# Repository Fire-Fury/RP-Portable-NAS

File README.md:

# RP-Portable-NAS
An attempt at making a personal cloud device with the form factor of a Raspberry Pi 4.

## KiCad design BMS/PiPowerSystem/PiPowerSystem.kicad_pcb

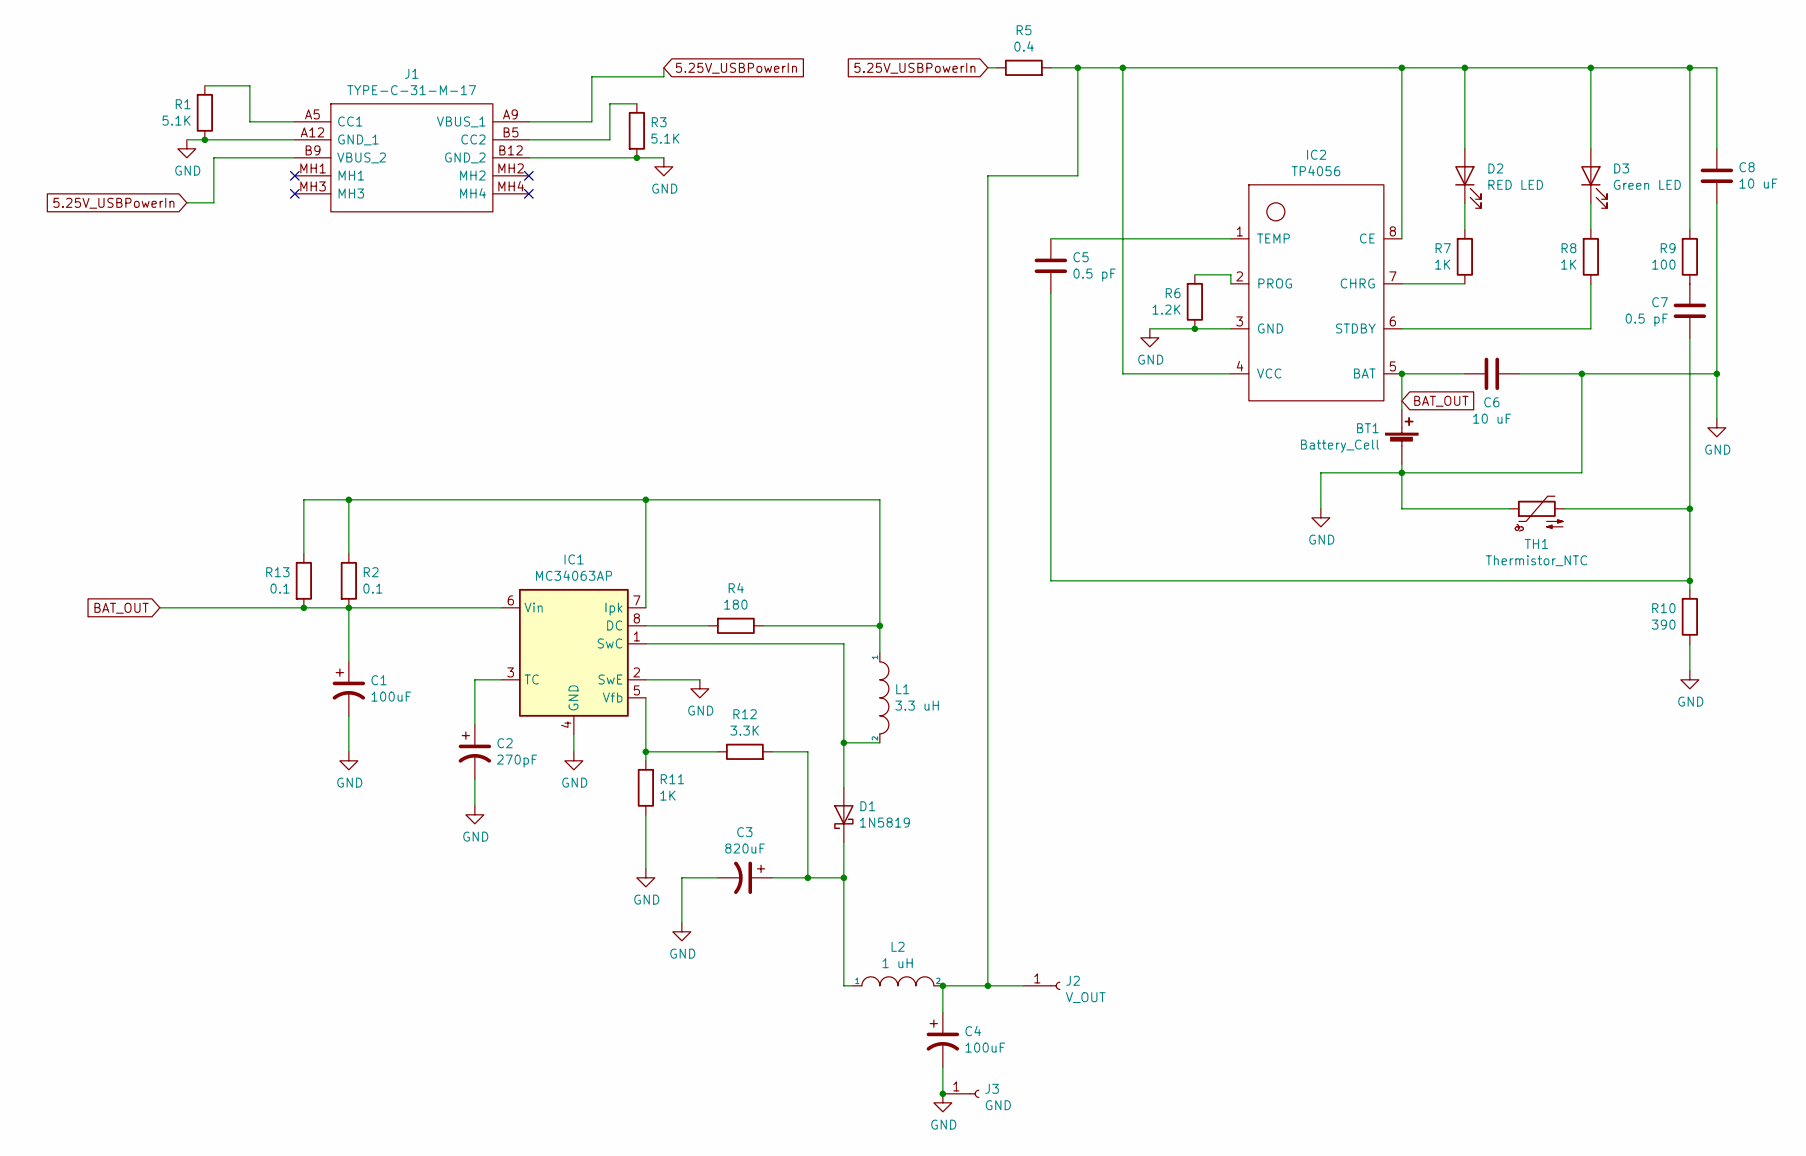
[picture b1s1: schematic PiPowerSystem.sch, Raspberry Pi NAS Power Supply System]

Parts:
BT1: Battery_Cell; JST_PH_B2B-PH-K_1x02_P2.00mm_Vertical
C1, C4: 100uF; CP_Radial_D8.0mm_P3.50mm
C2: 270pF; C_Disc_D5.1mm_W3.2mm_P5.00mm
C3: 820uF; CP_Radial_D10.0mm_P5.00mm
C5, C7: 0.5 pF; C_Disc_D3.4mm_W2.1mm_P2.50mm
C6, C8: 10 uF; CP_Radial_D4.0mm_P2.00mm
D1: 1N5819; D_DO-41_SOD81_P10.16mm_Horizontal
D2: RED LED; LED_D5.0mm
D3: Green LED; LED_D5.0mm
IC1: MC34063AP; DIP-8_W7.62mm
IC2: TP4056; SOIC127P600X175-9N
J1: TYPE-C-31-M-17; TYPEC31M17; Manufacturer_Part_Number TYPE-C-31-M-17
J2: V_OUT; PinHeader_1x01_P2.54mm_Vertical
J3: GND; PinHeader_1x01_P2.54mm_Vertical
L1: 3.3 uH; L_Axial_L5.0mm_D3.6mm_P10.00mm_Horizontal_Murata_BL01RN1A2A2
L2: 1 uH; L_Axial_L5.0mm_D3.6mm_P10.00mm_Horizontal_Murata_BL01RN1A2A2
R1, R3: 5.1K; R_Axial_DIN0204_L3.6mm_D1.6mm_P7.62mm_Horizontal
R2, R13: 0.1; R_Axial_DIN0204_L3.6mm_D1.6mm_P7.62mm_Horizontal
R4: 180; R_Axial_DIN0204_L3.6mm_D1.6mm_P7.62mm_Horizontal
R5: 0.4; R_Axial_DIN0204_L3.6mm_D1.6mm_P7.62mm_Horizontal
R6: 1.2K; R_Axial_DIN0204_L3.6mm_D1.6mm_P7.62mm_Horizontal
R7, R8, R11: 1K; R_Axial_DIN0204_L3.6mm_D1.6mm_P7.62mm_Horizontal
R9: 100; R_Axial_DIN0204_L3.6mm_D1.6mm_P7.62mm_Horizontal
R10: 390; R_Axial_DIN0204_L3.6mm_D1.6mm_P7.62mm_Horizontal
R12: 3.3K; R_Axial_DIN0204_L3.6mm_D1.6mm_P7.62mm_Horizontal
TH1: Thermistor_NTC; PinHeader_1x02_P2.54mm_Vertical

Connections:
5.25V_USBPowerIn: J1.A9 (VBUS_1), J1.B9 (VBUS_2), R5.1
BAT_OUT: BT1.1 (+), C1.1, C6.2, IC1.6 (Vin), IC2.5 (BAT), R2.2, R13.2
GND: BT1.2 (-), C1.2, C2.2, C3.2, C4.2, C6.1, C8.2, IC1.2 (SwE), IC1.4 (GND), IC2.3 (GND), J1.A12 (GND_1), J1.B12 (GND_2), J3.1, R1.1, R3.2, R6.1, R10.1, R11.1, TH1.1
unnamed: C2.1, IC1.3 (TC)
unnamed: C3.1, D1.1 (K), L2.1, R12.2
unnamed: C4.1, C8.1, D2.2 (A), D3.2 (A), IC2.4 (VCC), IC2.8 (CE), J2.1, L2.2, R5.2, R9.2
unnamed: C5.1, IC2.1 (TEMP)
unnamed: C5.2, C7.2, R10.2, TH1.2
unnamed: C7.1, R9.1
unnamed: D1.2 (A), IC1.1 (SwC), L1.2
unnamed: D2.1 (K), R7.2
unnamed: D3.1 (K), R8.2
unnamed: IC1.5 (Vfb), R11.2, R12.1
unnamed: IC1.7 (Ipk), L1.1, R2.1, R4.1, R13.1
unnamed: IC1.8 (DC), R4.2
unnamed: IC2.2 (PROG), R6.2
unnamed: IC2.6 (STDBY), R8.1
unnamed: IC2.7 (CHRG), R7.1
unnamed: J1.A5 (CC1), R1.2
unnamed: J1.B5 (CC2), R3.1

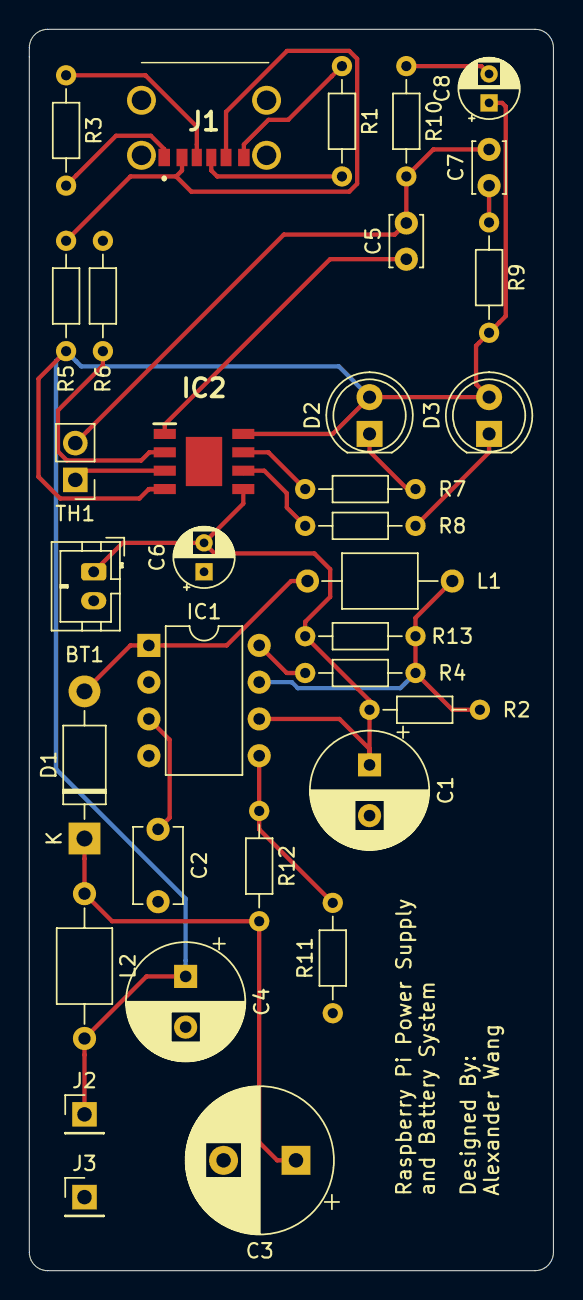
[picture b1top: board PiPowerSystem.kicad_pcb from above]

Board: 2 copper layers, 36.2 x 85.7 mm, 33 parts (0 on the bottom side), 20 nets.

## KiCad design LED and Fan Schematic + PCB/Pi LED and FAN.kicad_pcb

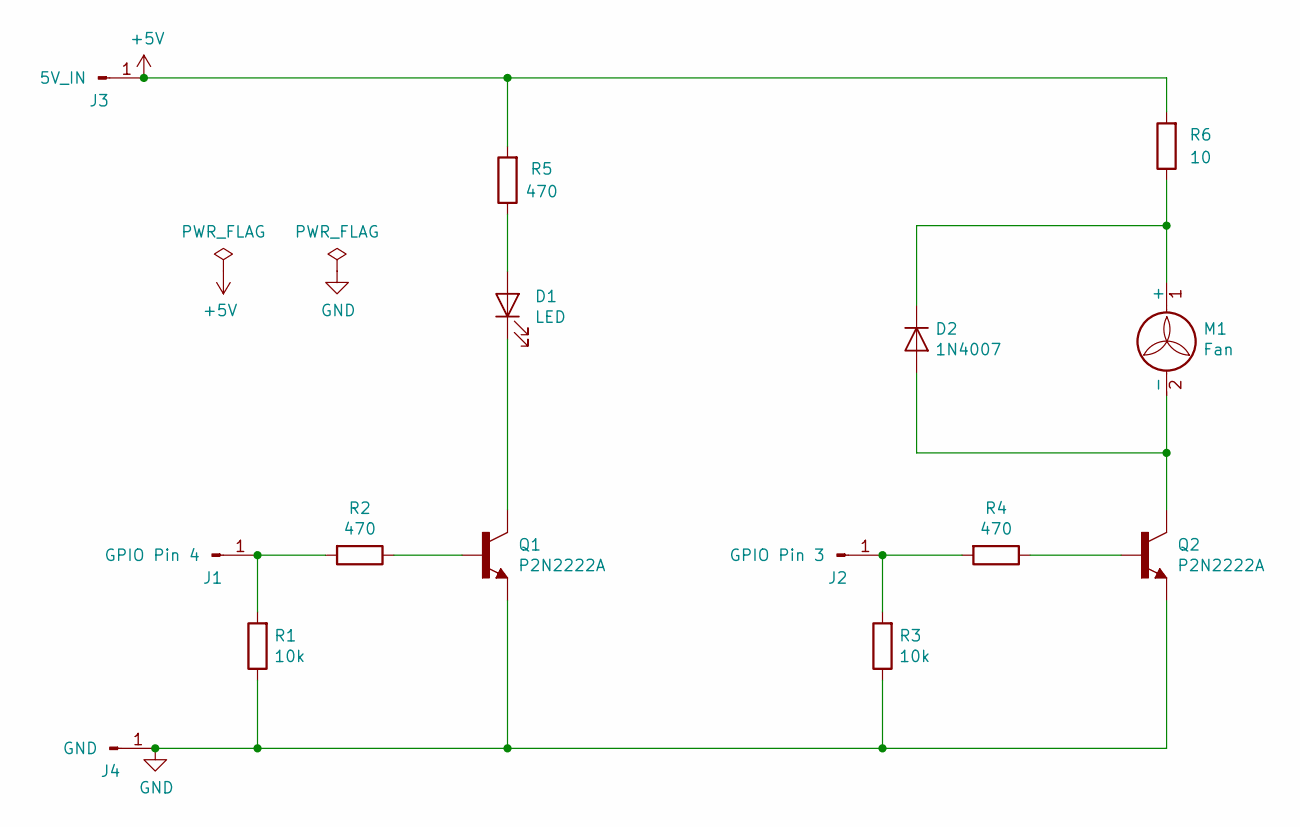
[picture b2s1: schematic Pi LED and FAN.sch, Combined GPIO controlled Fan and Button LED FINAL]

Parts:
D1: LED; PinHeader_1x02_P2.54mm_Vertical
D2: 1N4007; D_DO-41_SOD81_P10.16mm_Horizontal
J1: GPIO Pin 4; PinHeader_1x01_P2.54mm_Vertical
J2: GPIO Pin 3; PinHeader_1x01_P2.54mm_Vertical
J3: 5V_IN; PinHeader_1x01_P2.54mm_Vertical
J4: GND; PinHeader_1x01_P2.54mm_Vertical
M1: Fan; PinHeader_1x02_P2.54mm_Vertical
Q1, Q2: P2N2222A; TO92
R1, R3: 10k; R_Axial_DIN0204_L3.6mm_D1.6mm_P5.08mm_Horizontal
R2, R4, R5: 470; R_Axial_DIN0204_L3.6mm_D1.6mm_P5.08mm_Horizontal
R6: 10; R_Axial_DIN0204_L3.6mm_D1.6mm_P5.08mm_Horizontal

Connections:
+5V: J3.1, R5.2, R6.2
GND: J4.1, Q1.1 (E), Q2.1 (E), R1.1, R3.1
unnamed: D1.1 (K), Q1.3 (C)
unnamed: D1.2 (A), R5.1
unnamed: D2.1 (K), M1.1 (+), R6.1
unnamed: D2.2 (A), M1.2 (-), Q2.3 (C)
unnamed: J1.1, R1.2, R2.2
unnamed: J2.1, R3.2, R4.2
unnamed: Q1.2 (B), R2.1
unnamed: Q2.2 (B), R4.1

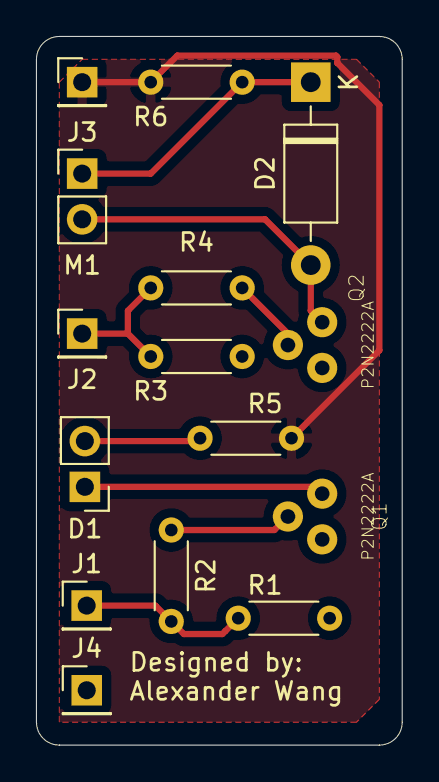
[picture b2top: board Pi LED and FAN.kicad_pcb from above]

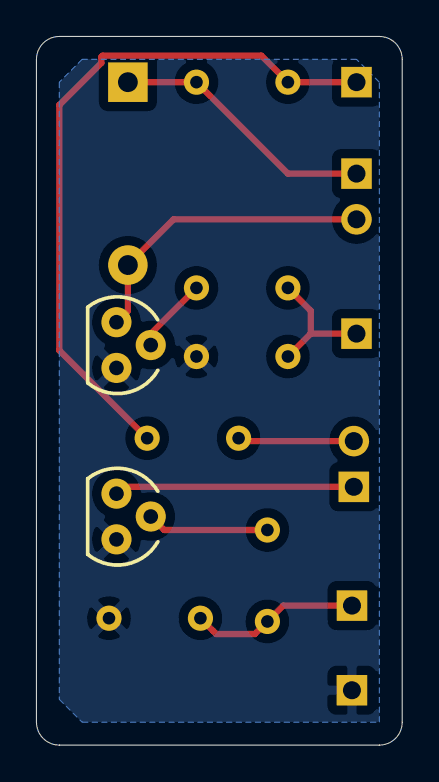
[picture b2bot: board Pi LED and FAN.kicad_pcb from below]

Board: 2 copper layers, 20.3 x 39.4 mm, 15 parts (2 on the bottom side), 10 nets.

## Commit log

2019-08-05 Added software regarding basic GPIO functionalities.
2019-08-05 added schematic for GPIO control of fan and on-off button LED
2019-08-05 Added folder for BMS design
2019-08-05 added html version
2019-08-05 some changes
2019-08-06 flashing light during startup
2019-08-07 began looking for components fo build BMS system
2019-08-10 made some changes to PCB schematic and code updated for new GPIO Pins
2019-08-17 finished BMS Mk 1 Circuit
2019-09-11 Added demo pictures and schematics
